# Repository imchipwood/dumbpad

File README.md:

dumbpad is a simple macropad with support for up to two rotary encoders, designed to use [QMK](https://qmk.fm/) firmware.

## Gallery

Top two boards are v0.2, bottom two are v0.7. Bottom right is v0.7 with components soldered to the bottom, moving the rotary encoder to the right side.

## In this repository

This repo is separated into five main folders:

- [combo](./combo) houses the main PCB design which includes support for up to two rotary encoders and three status LEDs intended for the Pro Micro.
- [combo_oled](./combo_oled) was created by [KEEBD](https://keebd.com) and replaces the layer LED/Resistors with OLED display support and converted to KiCad.
- [combo_oled_low_profile](./combo_low_profile_oled) Revision of [combo_oled](./combo_oled) with low profile hot swap sockets for Gateron v2 switches
- [combo_teensy](./combo_teensy) is the same as [combo](./combo) but designed for the Teensy2.0.
- [reversible](./reversible) is an older, single-encoder revision using custom reversible Cherry MX sockets to allow the rotary encoder to be moved to the right side.
- [hotswap_rgb - v3.x](./hotswap_rgb) dumbpad featuring per-key RGB and Hotswap sockets

Each folder includes the Eagle or KiCad files as well as exported Gerber files for manufacturing. These folders also include readmes specific to those designs - check them for more info.

## Getting Started
To build your own dumbpad you will need to follow a couple of steps to get started. Described below are the minimal steps you will need to take to to assemble one dumbpad but every board configuration might require different steps. 
#### 1. Choose version. 
You can choose from one of the five different versions shown in the step above.
#### 2. Order your parts. 
Every board needs at least the following components but check the right folder for your parts list.
* 1 x PCB
* 16 x MX-style mechanical switches
* 17 x 1n4148 diodes (thru hole)
* 1 x Arduino Pro Micro or pin-compatible ATmega32u4-based MCU (Or teensy for the teensy version)
* (optional) 1 x EC11 rotary encoder with pushbutton (7-pin)
* (optional) 1 x 6mm tactile switch (to reset MCU)
* LEDS and OLED required for different configurations

#### 3. Assemble your dumbpad
For this step you will need a minimum of a soldering iron and a pair of tweezers
- Solder the diodes, switches, and Arduino Pro Micro (Or teensy) to the PCB

#### 4. Flash your firmware
You can use QMK to create and flash firmware to your dumbpad. You can configure every key to you can use the QMK configurator. Head over to the [QMK configurator](https://config.qmk.fm/#/friedrich/LAYOUT) and select dumbpad/[your version]. Once you have configured your board, click on compile and then on firmware to download the firmware. Check [qmk_firmware/keyboards/dumbpad](https://github.com/qmk/qmk_firmware/tree/master/keyboards/dumbpad) for compiling & uploading instructions

Once you have downloaded a .HEX firmware file we can head over to the [QMK toolbox](https://github.com/qmk/qmk_toolbox/releases) and flash the firmware. Plug in your dumbpad to your computer and set your QMK toolbox to ATmega32U4 for most Arduino Pro Micros. You will need to press your 6mm tacticle switch twice to enter the bootloader, wait for your computer to recognize the dumbpad and click on flash.

### Features

#### Status Indicator LEDs

All PCB revisions in this branch support up to three LEDs.

| LED position on PCB | LED name in QMK software | LED default behavior |
|:-:|:-:|:-:|
| right | LED_00 | 1s bit in binary layer indication |
| center | LED_01 | 2s bit in binary layer indication |
| left | LED_02 | numlock indicator |

LED_00 (right) and LED_01 (center) indicate the layer by displaying the layer number in binary:

| center LED | right LED  |   layer    |
|:----------:|:----------:|:----------:|
| off        | off        | 0 (main)   |
| off        |  on        | 1          |
|  on        | off        | 2          |
|  on        |  on        | 3          |

LED behavior can be changed in the QMK software if you'd like them to do something else. See [v1x.c](https://github.com/imchipwood/qmk_firmware/blob/dumbpad_refactor/keyboards/dumbpad/v1x/v1x.c) for reference.

#### (Optional) Reset Button

[combo](./combo), [hotswap_rgb](./hotswap_rgb) and [reversible](./reversible) have a 6mm switch socket that is optional to include when building your dumbpad. This socket shorts RST to GND to make it easy to enter the bootloader. This is not included in the [combo_teensy](./combo_teensy) design as the Teensy has a reset button already.

If you don't want to solder this switch, make sure to include the [RESET](https://docs.qmk.fm/#/quantum_keycodes) keycode somewhere in your keymap. If you don't include this keycode, you can still enter the bootloader by shorting RST to GND while plugging in the USB cable.

## PCB Dimensions and Cases

97mm x 78.5mm rectangle, with chamfered corners (chamfered edge is 2.828mm long).

There are several cases available for printing, some can be found in `./case`. Another nice case was designed by [f00k3r](https://twitter.com/f00k3r) and uploadead to printables: [Dumbpad Hotswap Case](https://www.printables.com/model/200528-dumbpad-hotswap-case).

### Mounting holes

There are four 2mm holes in a 40mm square centered at (x, y) 58.575mm, 39.425mm. These holes are not plated.

Mounting hole coordinates:

| x (mm) | y (mm) |
|:------:|:------:|
| 38.575 | 19.425 |
| 38.575 | 59.425 |
| 78.575 | 19.425 |
| 78.575 | 59.425 |

## Notes

- In particular, clickable rotary encoders take significantly more force to click than a keyboard switch, so place a rubber foot directly under or at least near any encoders

## Making the PCB

Every parts list includes at least one PCB. You can order a PCb yourself by different manufactures like; [PCB way](https://www.pcbway.com/) or [JLC Pcb](https://jlcpcb.com/) Submit one of the gerber zips from the folder of the type of board you want to make to your preferred manufacturer (or the Eagle .brd file if supported).

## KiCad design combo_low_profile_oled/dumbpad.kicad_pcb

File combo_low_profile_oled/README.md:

# dumbpad - Low Profile OLED (aka v1.3)

Modified by [ReyvanZA]

## Description

Version of the original dumbpad but with support for an OLED display by Keebd, now with gateron low profile hot swap sockets.
There are also mounting points for a uController cover, and through holes for wires if using a ProMicro nrf52840 for the battery wires (admittedly not overly practical).

Only 1.3.1 has been tested with the gateron low profile hot-swap sockets. The gerber files included (see manufacturing notes at the end)

### Revisions

- 1.2 Keebd OLED with resistors
- 1.3.1 Gateron low profile hot-swap sockets (Confirmed working - need low profile keys to test)
- 1.3.2 (Untested) Combined plated though holes for EC11 rotary encoder mounting points and socket, added mounting holes for uController cover. Placed resistors on back of PCB so I can use an alignment plate for the switches to hold them more steadily.

### References

- Gateron low profile hot-swap sockets: https://gist.github.com/niw/22c68c2d7c869b990588b4875a654442

#### dumbpad v1.3.1

#### Renders (Latest Revision)

### Bill of materials
- 1 x PCB
- 16 x Gateron low profile switches (Link)
- 16 x Gateron low profile hot-swap sockets (Link)
- X x Keycaps (compatible with Gateron low profile switches)
- 17 x 1n4148 diodes (thru hole)
- 1 x Arduino Pro Micro or pin-compatible ATmega32u4-based MCU (Or teensy for the teensy version)
- 1 x or 2x EC11 rotary encoder with pushbutton (7-pin)
- 1 x 6mm tactile switch (to reset MCU)
- 1 x 0.91" 128X32 OLED Display (Optional)

## OLED Firmware

The OLED firmware is different and can be found here [Firmware](https://docs.keebd.com/firmware/)

## How to build 
- Be very careful when soldering pads next to rotary encoder through holes (encoder pin b), you may get bridging.
- I've moved the pin slightly closer to the ground pin to aleviate this issue. This does not affect assembly.

You can follow the instructions from the main [readme](https://github.com/imchipwood/dumbpad#getting-started) or follow the instruction in this [blog](https://www.timowielink.com/post/how-to-build-a-macropad) from [Timo Wielink](https://github.com/TimoWielink)

When the 1.3.1 production file is created by your PCB manufacturer, you may have a query on the overlapping through holes. If given the option allow them to plate both holes.

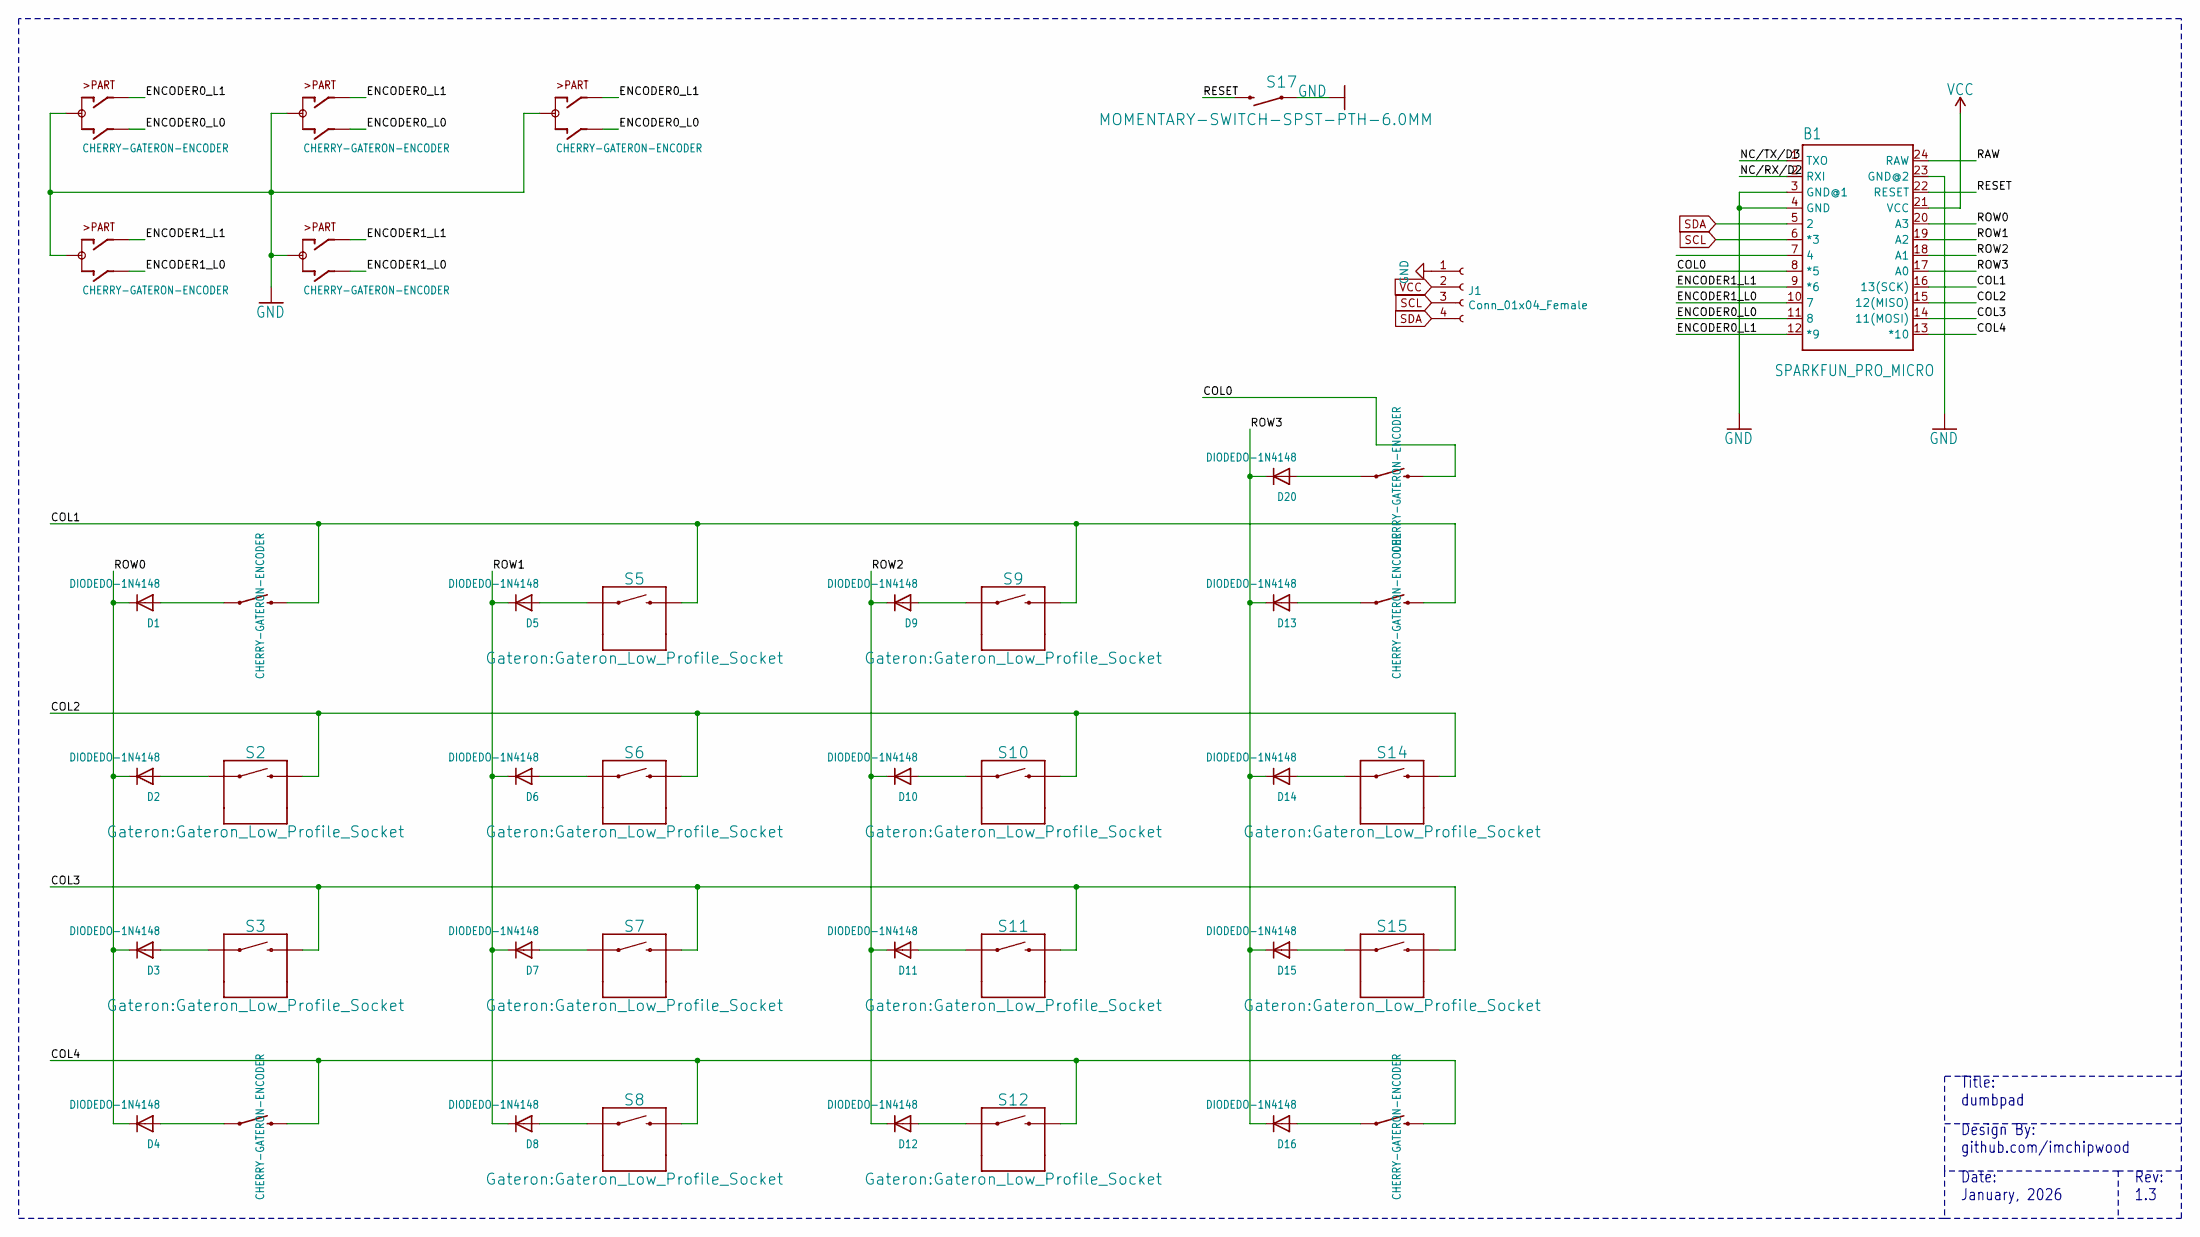
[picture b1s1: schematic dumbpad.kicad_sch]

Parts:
B1: SPARKFUN_PRO_MICRO
D1, D2, D3, D4, D5, D6, D7, D8, D9, D10, D11, D12, D13, D14, D15, D16, D20: DIODEDO-1N4148; DO-1N4148
J1: Conn_01x04_Female; OLED
RE_0_1, RE_0_4, RE_3_0, RE_3_1, RE_3_4: CHERRY-GATERON-ENCODER
S2, S3, S5, S6, S7, S8, S9, S10, S11, S12, S14, S15: Gateron:Gateron_Low_Profile_Socket; Gateron_Low_Profile_Socket
S17: MOMENTARY-SWITCH-SPST-PTH-6.0MM; TACTILE_SWITCH_PTH_6.0MM

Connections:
/COL0: B1.8 (*5), RE_3_0.E (2), RE_3_0.S2 (2)
/COL1: B1.16 (13(SCK)), RE_0_1.E (2), RE_0_1.S2 (2), RE_3_1.E (2), RE_3_1.S2 (2), S5.S2 (2), S9.S2 (2)
/COL2: B1.15 (12(MISO)), S2.S2 (2), S6.S2 (2), S10.S2 (2), S14.S2 (2)
/COL3: B1.14 (11(MOSI)), S3.S2 (2), S7.S2 (2), S11.S2 (2), S15.S2 (2)
/COL4: B1.13 (*10), RE_0_4.E (2), RE_0_4.S2 (2), RE_3_4.E (2), RE_3_4.S2 (2), S8.S2 (2), S12.S2 (2)
/ENCODER0_L0: B1.11 (8), RE_0_1.B, RE_3_0.B, RE_3_1.B
/ENCODER0_L1: B1.12 (*9), RE_0_1.A, RE_3_0.A, RE_3_1.A
/ENCODER1_L0: B1.10 (7), RE_0_4.B, RE_3_4.B
/ENCODER1_L1: B1.9 (*6), RE_0_4.A, RE_3_4.A
/NC/RX/D2: B1.2 (RXI)
/NC/TX/D3: B1.1 (TXO)
/RAW: B1.24 (RAW)
/RESET: B1.22 (RESET), S17.3 (2)
/ROW0: B1.20 (A3), D1.C, D2.C, D3.C, D4.C
/ROW1: B1.19 (A2), D5.C, D6.C, D7.C, D8.C
/ROW2: B1.18 (A1), D9.C, D10.C, D11.C, D12.C
/ROW3: B1.17 (A0), D13.C, D14.C, D15.C, D16.C, D20.C
GND: B1.3 (GND@1), B1.4 (GND), B1.23 (GND@2), J1.1, RE_0_1.C, RE_0_4.C, RE_3_0.C, RE_3_1.C, RE_3_4.C, S17.1
unnamed: D1.A, RE_0_1.D (1), RE_0_1.S1 (1)
unnamed: D4.A, RE_0_4.D (1), RE_0_4.S1 (1)
unnamed: D13.A, RE_3_1.D (1), RE_3_1.S1 (1)
unnamed: D16.A, RE_3_4.D (1), RE_3_4.S1 (1)
unnamed: D20.A, RE_3_0.D (1), RE_3_0.S1 (1)
unnamed: D2.A, S2.S1 (1)
unnamed: D3.A, S3.S1 (1)
unnamed: D5.A, S5.S1 (1)
unnamed: D6.A, S6.S1 (1)
unnamed: D7.A, S7.S1 (1)
unnamed: D8.A, S8.S1 (1)
unnamed: D9.A, S9.S1 (1)
unnamed: D10.A, S10.S1 (1)
unnamed: D11.A, S11.S1 (1)
unnamed: D12.A, S12.S1 (1)
unnamed: D14.A, S14.S1 (1)
unnamed: D15.A, S15.S1 (1)
SCL: B1.6 (*3), J1.3
SDA: B1.5 (2), J1.4
VCC: B1.21 (VCC), J1.2

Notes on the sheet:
Title: dumbpad
Design By: github.com/imchipwood
Rev: 1.3
Date: January, 2026

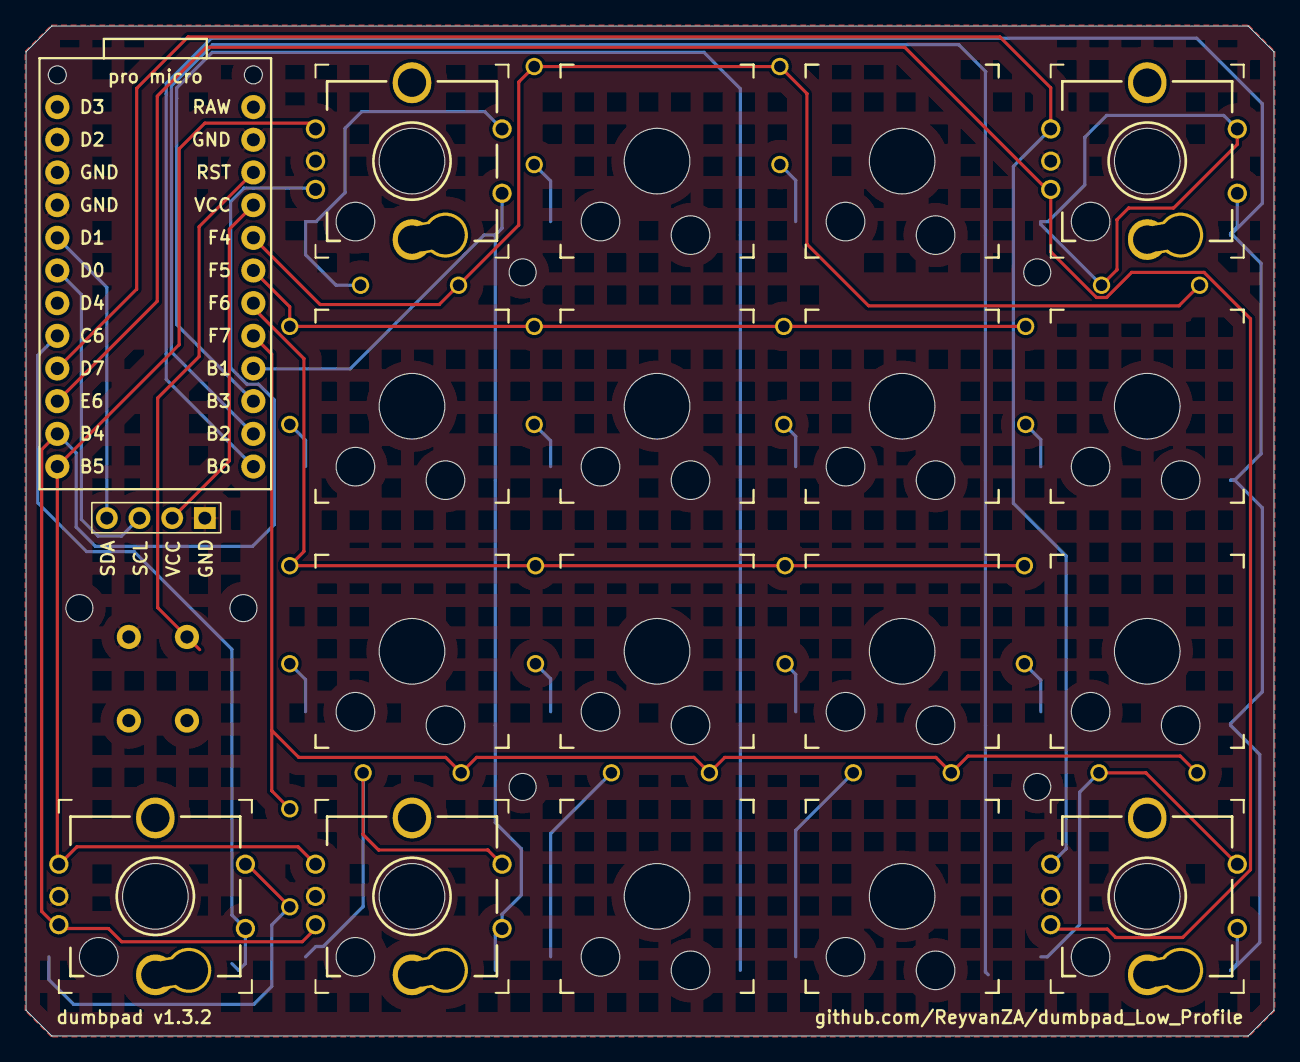
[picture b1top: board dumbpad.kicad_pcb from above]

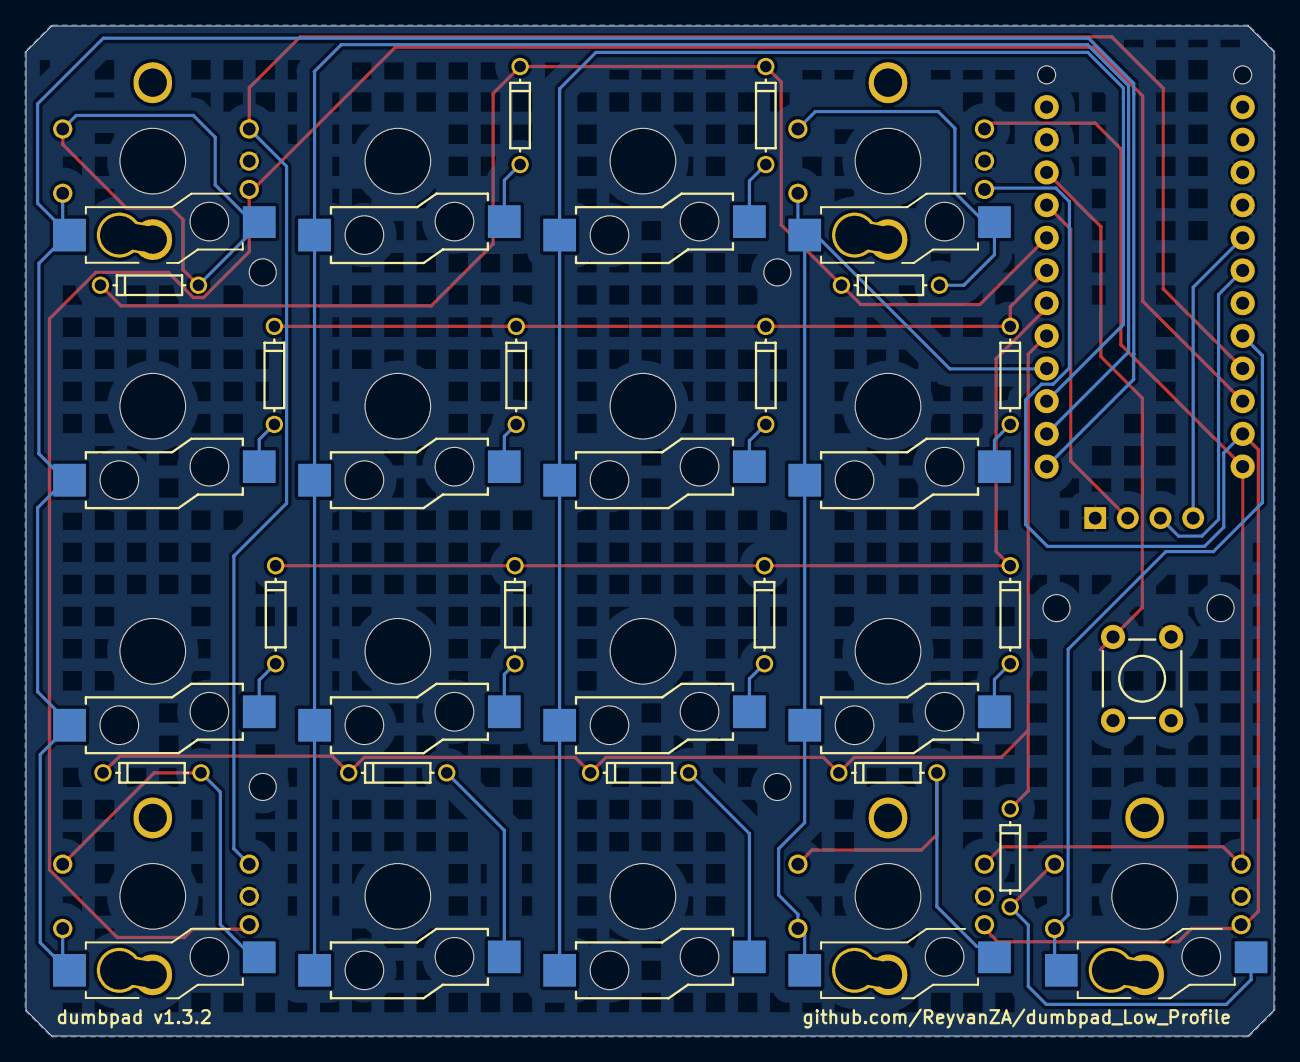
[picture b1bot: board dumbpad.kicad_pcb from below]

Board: 2 copper layers, 97.0 x 78.5 mm, 43 parts (18 on the bottom side), 35 nets.

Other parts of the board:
MH1, MH1#2, MH1#3, MH2, MH3, MH4: MountingHole_2.1mm

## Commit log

2019-07-03 adding readme
2019-07-14 diodes...
2019-07-14 tweaks
2019-07-14 moved email/name thing
2019-07-14 added reset button, centered diodes on switches
2019-07-14 ignore eagle temp files
2019-07-14 updated README with switch
2019-07-14 minor tweaks, sch as png
2019-07-14 name/contact info on both sides, some pro micro pins labeled to ensure it's not mounted incorrectly
2019-07-14 added labels to all pro micro pins
2019-07-14 shrinking, aligning
2019-07-14 removed resistors from rotary encoder, updated readme
2019-07-28 moved all components to top, rerouted
2019-07-28 slight tweaks to spacing, orientation of one diode, etc.
2019-07-28 v0.4 done - moved diodes to right side of switches for cleaner routing. Adjusted dimension slightly to give more room around switches so keycaps don't hang over the sides
2019-07-28 updated readme with image and some other info
2019-07-28 whoops messed up markdown image
2019-07-28 added GPL
2019-07-28 updated gitignore
2019-07-28 more tweaks to v4 for A E S T H E T I C
2019-07-29 who doesn't like LEDs
2019-08-03 final touches to v0.5
2019-08-03 updated readme for v0.5 - 2x LEDs, 2x resistors
2019-08-04 added Open Source Hardware logo to tplace and bplace
2019-08-04 added screenshot to readme
2019-08-04 added screenshot of layout and put it in the readme
2019-08-04 removed top OSHW silk, adding reset button back shortly
2019-08-04 added reset button back to v0.5
2019-08-04 minor tweak to routing
2019-08-05 way too many vias... but it's routed
2019-08-06 some rerouting to reduce vias and clean things up a tad
2019-08-06 updated readme and screenshot
2019-08-06 added LEDs to README
2019-08-30 dual encoders on the bottom, need to add mirror switches
2019-08-30 updated readme, added reversible switch sockets so PCB can be soldered to from either side
2019-08-30 merging v05 into master manually
2019-08-30 using reversible sockets
2020-01-18 moved encoders to the top
2020-01-18 updated board screenshot
2020-03-20 added dual-encoder image from someone who actually made one
2020-04-11 added jumpers for reversing encoder when using encoder on right side instead of left
2020-04-11 updated revision to v0.7
2020-04-12 merging v08_jumpers to master
2020-04-15 updated readme and added board layout screenshot
2020-04-15 updated README and added screenshot of board layout
2020-04-15 updated v0.5 readme
2020-04-15 fixed error in readme
2020-04-15 moved some wires to avoid sketchy tolerances and updated readme
2020-04-15 replaced reversible sockets with normal cherry sockets, rerouted some stuff, updated readme and screenshot
2020-04-22 added 3rd LED for numlock indication
2020-04-24 moved LEDs, added more gs
2020-04-24 made reversible sockets show outline on tplace and bplace
2020-04-29 updated readme, made jumpers a little bigger for easier soldering, updated version to 1.0
2020-05-02 swapped some LED pins to make the first two LEDs connecting to the same pins as v0.x PCBs
2020-05-06 all parts have bottom silk screen now, rerouted some stuff
2020-05-06 added mounting holes
2020-05-06 added notes to readme about mounting holes
2020-05-06 fixed issue with wrong jumper size
2020-05-06 replaced image in readme
2020-05-07 v1.0 dual encoder version with debug headers
2020-05-17 non-debug version of dualencoder layout
2020-05-17 minor tweaks
2020-05-17 changed mounting holes to 40mm square
2020-05-17 changed mounting holes to 40mm
2020-05-17 updated readme for mounting holes
2020-05-17 readme formatting fix
2020-05-21 dualencoder now has cherry/encoder sockets for putting encoders on either top row or bottom row
2020-05-21 dual + single encoder configuration
2020-05-21 updating board and adding cam file
2020-05-21 updating gitignore, updating board png
2020-05-21 minor changes
2020-05-22 long pads with mill
2020-05-22 rerouted some stuff
2020-05-22 organized schematic, silkscreen tweaks,
2020-05-22 rerouted and moved things around, updated readme
2020-05-30 gerbers for v1.0 board
2020-05-30 adding gerbers, got slots working, updated readme
2020-05-30 removed cam file, v1.0 gerbers
2020-05-30 removed bottomsilk screenshot
2020-05-31 master now contains all variations of the board, organized into their own folders
2020-05-31 updated readmes and whatnot
2020-05-31 forgot to save readme...
2020-06-01 updated library for combo_teensy
2020-06-01 added gerbers for teensy
2020-06-01 added some images of the possible layouts to combo/README.md
2020-06-01 fixing bad merge
2020-06-01 fixing naming issue in combo
2020-06-01 matching reversible version encoder pins to combo
2020-06-01 fixed encoder pin naming mismatch, updated screenshot
2020-06-01 updated combo gerbers
2020-06-01 updated reversible gerbers
2021-04-01 copying initial case files from other repo
2021-04-01 updated case to have slight relief for usb cable
2021-04-02 adding embossed version
2021-04-04 Fixing qmk links
2021-04-04 updated usb port relief area
2021-04-04 updated combo readme
2021-04-04 updated readme, removed unused stl
2021-04-04 added thingiverse link to case to readmes
2021-04-04 fixed thingiverse link
2021-09-22 added plate stl files & plate readme
2021-09-22 added stl files and readme for plates
2021-09-22 added thingiverse link to readme
2021-09-23 updated plate thickness
2022-01-22 convert from Eagle to KiCad and replaced LEDs for OLED Display
2022-01-22 added combo_oled designed by KEEBD to the README
2022-02-09 Dumbpad with RGB and Hotswap
2022-02-09 v3.x: Add Gerberfiles
2022-02-11 Update images
2022-02-18 Dumbpad v3: cleanup dependencies
2022-04-03 Add VIA configuration for dumbpad v3
2022-04-26 Add README with images and info for the Dumbpad OLED
2022-04-26 settings adjustments
2022-04-26 Add Firmware details to dumbpad_oled README
2022-04-28 fix schematic and remove missing drawing sheet
2022-04-28 changed the USB cable relief slightly - less depth, looking to rest the cable on the case a bit (have had some troubles with the micro USB port eventually falling off on my oldest dumbpads)
2022-04-29 add missing mounting holes from the conversion
2022-04-29 update gerber zip with change adding mount holes back
2022-05-09 Add notes to Case Options
2022-05-23 Fix link to full plate stl
2022-10-11 feat: add firmware and update readme.md
2023-01-31 Fixed spelling on line 44
    Line 44 had the spelling baord, fixed it to board
2024-05-21 added note regarding non-plated through-holes
    ... which will potentially throw red flags for manufacturers
2024-06-19 Added new case designs
2026-03-03 Added images for completed keypad v1.3.1
2026-03-03 Readme wording.
2026-06-26 fix typo: reconize -> recognize in README.md
